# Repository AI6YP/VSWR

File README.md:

# VSWR
VSWR / Return loss analyzer

## Schematic

## PCB

### Top

### Bottom

## Parts

| pos | type | size | value |
|-----|------|------|-------|
| C6, C8, C13, C14 | NP0 | 0603 | 100pF |
| C11, C15 | X7R | 0603 | 0.1uF |
| C12, C16 | NP0 | 0603 | 100nF |
| R9, R13 | RC | 0603 | 100 |
| R9a, R13a | RC | 0603 | 110 |
| R11, R12 | RC | 0603 | 1K |

### Directional coupler

### RMS Power Detector
LTC5587

Name                                             | $     | Frequency     | Input Range    | Package  | Interface
------------------------------------------------ | ----- | ------------- | -------------- | -------- | ---------
[LMH2110TM](http://www.digikey.com/short/tc024d) | 2.30  | 50MHz ~ 8GHz  | -40dBm ~ 5dBm  | 6-WFBGA  | analog
[LTC5531](http://www.digikey.com/short/tc02f4)   | 3.07  | 300MHz ~ 7GHz | -32dBm ~ 10dBm | SOT-23-6 | analog
[AD8317](http://www.digikey.com/short/t7rp3d)    | 9.75  | 1MHz ~ 10GHz  | -53dBm ~ -3dBm | 8-VFDFN  | analog
[AD8319](http://www.digikey.com/short/tc02hf)    | 4.84  | 1MHz ~ 10GHz  | -43dBm ~ -3dBm | 8-VFDFN  | analog
[LTC5587](http://www.digikey.com/short/tc02dt)   | 11.03 | 10MHz ~ 6GHz  | -34dBm ~ 6dBm  | 12-WFDFN | SPI

### RF Synthesizer/VCO

Name                                           | $     | Frequency        | Package | Interface
---------------------------------------------- | ----- | ---------------- | ------- | ---------
[MAX2871](http://www.digikey.com/short/t7rz2d) | 11.12 | 23.5 .. 6000 MHz | TQFN-32 | SPI
[LMX2592](http://www.digikey.com/short/3j1prr) | 36.72 | 20 .. 9800 MHz   | WQFN-40 | SPI
[LMX2582](http://www.digikey.com/short/3j1p25) | 20.49 | 20 .. 5500 MHz   | WQFN-40 | SPI

### WiFi interface
[ESP8266 SMD board](http://www.electrodragon.com/w/ESP8266_SMD_Board) board $4

[ESP-12E](http://www.electrodragon.com/product/esp-12e-esp8266-wifi-board/) / [ESP-13](http://www.electrodragon.com/product/esp-13-esp8266-wifi-board/)

### Power

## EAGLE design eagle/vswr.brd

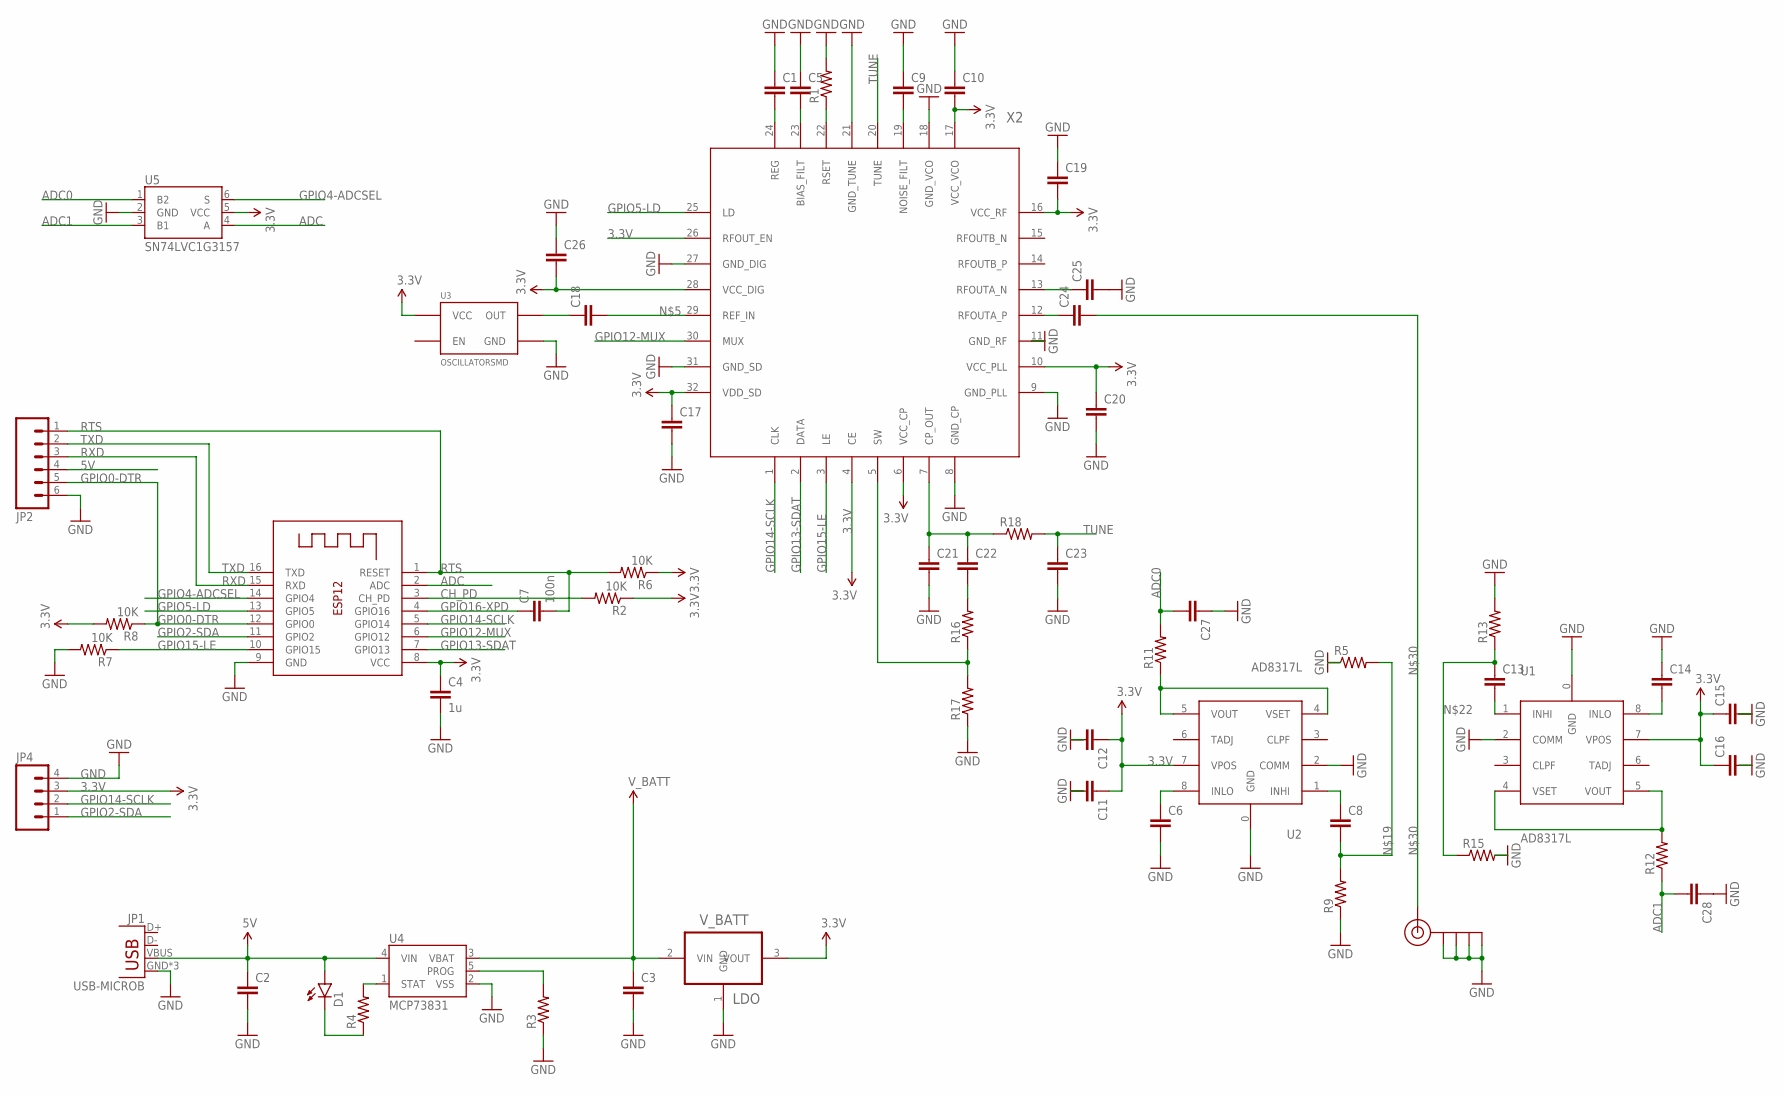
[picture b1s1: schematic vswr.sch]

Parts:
C1, C5, C6, C8, C9, C10, C11, C13, C14, C15, C17, C18, C19, C20, C24, C25, C26: CAP0402; 0402
C2, C3, C12, C16, C21, C22, C23, C27, C28: CAP0603; 0603
C4: 1u; 0603
C7: 100n; 0603
D1: LED0603; LED-0603
J$1: SMA_EDGE; SMA-EDGE
JP1: USB-MICROB
JP2: M061X06-SMD_EDGE_FEMALE; 1X06-SMD_EDGE
JP4: M04PTH; 1X04
R1, R5, R9, R13, R15, R16, R17, R18: RESISTOR0402; 0402
R2, R6, R7, R8: 10K; 0603
R3, R4, R11, R12: RESISTOR0603; 0603
U1, U2: AD8317L; DFN-8-EXTRA
U3: OSCILLATORSMD; CRYSTAL-SMD-7X5
U4: MCP73831; SOT23-5
U5: SN74LVC1G3157; SOT23-6
V_BATT: LDO; SOT89R
X1: ESP-12
X2: MAX2870TQFN-32-EXTRA; TQFN-32-EXTRA

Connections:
3.3V: C4.1, C10.2, C11.1, C12.1, C15.1, C16.1, C17.1, C19.2, C20.1, C26.2, JP4.3, R2.1, R6.1, R8.2, U1.7 (VPOS), U2.7 (VPOS), U3.P$4 (VCC), U5.5 (VCC), V_BATT.3 (VOUT), X1.8 (VCC), X2.4 (CE), X2.6 (VCC_CP), X2.10 (VCC_PLL), X2.16 (VCC_RF), X2.17 (VCC_VCO), X2.26 (RFOUT_EN), X2.28 (VCC_DIG), X2.32 (VDD_SD)
5V: C2.1, D1.A, JP1.VBUS, JP2.4, U4.4 (VIN)
ADC: U5.4 (A), X1.2 (ADC)
ADC0: C27.2, R11.2, U5.1 (B2)
ADC1: C28.2, R12.1, U5.3 (B1)
CH_PD: R2.2, X1.3 (CH_PD)
GND: C1.1, C2.2, C3.2, C4.2, C5.1, C6.2, C9.1, C10.1, C11.2, C12.2, C14.1, C15.2, C16.2, C17.2, C19.1, C20.2, C21.2, C23.2, C25.2, C26.1, C27.1, C28.1, J$1.GND@0 (GND), J$1.GND@1 (GND), J$1.GND@2 (GND), J$1.GND@3 (GND), JP1.GND, JP1.MT1 (GND), JP1.MT2 (GND), JP2.6, JP4.4, R1.2, R3.1, R5.1, R7.2, R9.1, R13.2, R15.2, R17.1, U1.0 (GND), U1.2 (COMM), U2.0 (GND), U2.2 (COMM), U3.P$2 (GND), U4.2 (VSS), U5.2 (GND), V_BATT.1 (GND), X1.9 (GND), X2.8 (GND_CP), X2.9 (GND_PLL), X2.11 (GND_RF), X2.18 (GND_VCO), X2.21 (GND_TUNE), X2.27 (GND_DIG), X2.31 (GND_SD)
GPIO0-DTR: JP2.5, R8.1, X1.12 (GPIO0)
GPIO2-SDA: JP4.1, X1.11 (GPIO2)
GPIO4-ADCSEL: U5.6 (S), X1.14 (GPIO4)
GPIO5-LD: X1.13 (GPIO5), X2.25 (LD)
GPIO12-MUX: X1.6 (GPIO12), X2.30 (MUX)
GPIO13-SDAT: X1.7 (GPIO13), X2.2 (DATA)
GPIO14-SCLK: JP4.2, X1.5 (GPIO14), X2.1 (CLK)
GPIO15-LE: R7.1, X1.10 (GPIO15), X2.3 (LE)
GPIO16-XPD: C7.1, X1.4 (GPIO16)
unnamed: C1.2, X2.24 (REG)
unnamed: C5.2, X2.23 (BIAS_FILT)
unnamed: C9.2, X2.19 (NOISE_FILT)
unnamed: C18.2, X2.29 (REF_IN)
unnamed: D1.C, R4.1
unnamed: C13.2, U1.1 (INHI)
unnamed: R1.1, X2.22 (RSET)
unnamed: C6.1, U2.8 (INLO)
unnamed: C25.1, X2.13 (RFOUTA_N)
unnamed: C8.1, U2.1 (INHI)
unnamed: C8.2, R5.2, R9.2
unnamed: R11.1, U2.4 (VSET), U2.5 (VOUT)
unnamed: C18.1, U3.P$3 (OUT)
unnamed: C13.1, R13.1, R15.1
unnamed: C21.1, C22.1, R18.1, X2.7 (CP_OUT)
unnamed: C24.1, X2.12 (RFOUTA_P)
unnamed: C14.2, U1.8 (INLO)
unnamed: C22.2, R16.2
unnamed: R12.2, U1.4 (VSET), U1.5 (VOUT)
unnamed: R16.1, R17.2, X2.5 (SW)
unnamed: C24.2, J$1.SIG (SIGNAL)
PROG: R3.2, U4.5 (PROG)
RTS: C7.2, JP2.1, R6.2, X1.1 (RESET)
RXD: JP2.3, X1.15 (RXD)
STAT: R4.2, U4.1 (STAT)
TUNE: C23.1, R18.2, X2.20 (TUNE)
TXD: JP2.2, X1.16 (TXD)
V_BATT: C3.1, U4.3 (VBAT), V_BATT.2 (VIN)

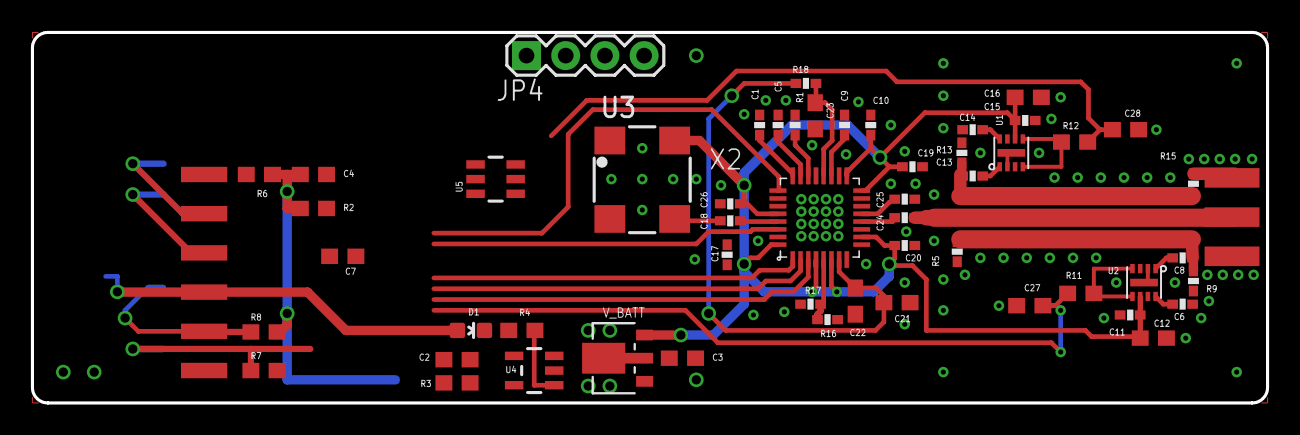
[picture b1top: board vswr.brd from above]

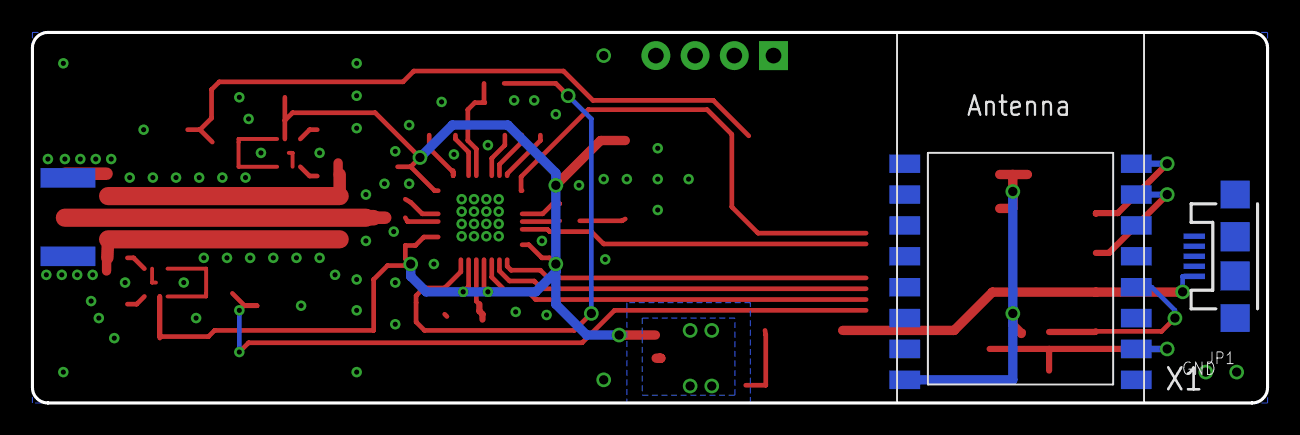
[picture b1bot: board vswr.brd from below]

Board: 2 copper layers, 80.0 x 24.0 mm, 57 parts (2 on the bottom side), 44 nets.

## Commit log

2015-07-04 added eagle library
2015-07-04 added schematics
2015-07-04 minor fix
2015-07-04 changed the esp picture
2015-07-21 added initial schematic and pcb files
2015-07-21 added pcb images
2017-09-18 correct ic property

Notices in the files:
parts and their libraries:
SparkFun: Licensing: CC v3.0 Share-Alike You are welcome to use this library for commercial purposes.
